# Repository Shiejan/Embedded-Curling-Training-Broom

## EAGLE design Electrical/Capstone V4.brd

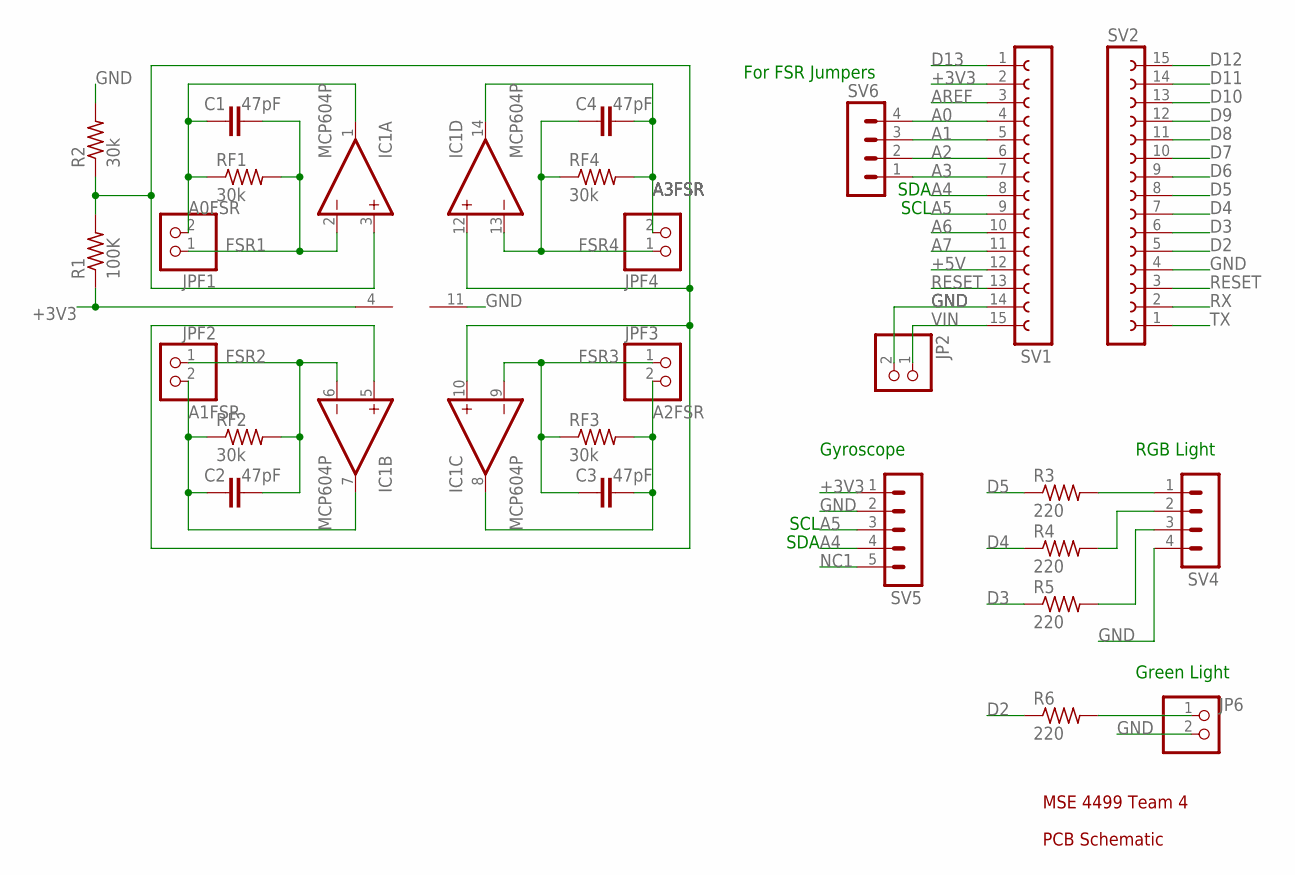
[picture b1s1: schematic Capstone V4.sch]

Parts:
C1, C2, C3, C4: 47pF; C2.5-3
IC1: MCP604P; DIL14
JP2, JP6: PINHD-1X2; 1X02
JPF1, JPF2, JPF3, JPF4: PINHD-1X2; 1X02
R1: 100K; 0204/7
R2: 30k; 0204/7
R3, R4, R5, R6: 220; 0204/7
RF1, RF2, RF3, RF4: 30k; 0204/7
SV1, SV2: FE15-1; FE15
SV4, SV6: MA04-1
SV5: MA05-1

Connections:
+3V3: IC1.4 (V+), R1.1, SV1.2, SV5.1
+5V: SV1.12
A0: SV1.4, SV6.4
A0FSR: C1.1, IC1.1 (OUT), JPF1.2, RF1.1
A1: SV1.5, SV6.3
A1FSR: C2.1, IC1.7 (OUT), JPF2.2, RF2.1
A2: SV1.6, SV6.2
A2FSR: C3.2, IC1.8 (OUT), JPF3.2, RF3.2
A3: SV1.7, SV6.1
A3FSR: C4.2, IC1.14 (OUT), JPF4.2, RF4.2
A4: SV1.8, SV5.4
A5: SV1.9, SV5.3
A6: SV1.10
A7: SV1.11
AREF: SV1.3
D2: R6.1, SV2.5
D3: R5.1, SV2.6
D4: R4.1, SV2.7
D5: R3.1, SV2.8
D6: SV2.9
D7: SV2.10
D8: SV2.11
D9: SV2.12
D10: SV2.13
D11: SV2.14
D12: SV2.15
D13: SV1.1
FSR1: C1.2, IC1.2 (-IN), JPF1.1, RF1.2
FSR2: C2.2, IC1.6 (-IN), JPF2.1, RF2.2
FSR3: C3.1, IC1.9 (-IN), JPF3.1, RF3.1
FSR4: C4.1, IC1.13 (-IN), JPF4.1, RF4.1
GND: IC1.11 (V-), JP2.2, JP6.2, R2.2, SV1.14, SV2.4, SV4.4, SV5.2
unnamed: R3.2, SV4.1
unnamed: R4.2, SV4.2
unnamed: R5.2, SV4.3
unnamed: JP6.1, R6.2
unnamed: IC1.3 (+IN), IC1.5 (+IN), IC1.10 (+IN), IC1.12 (+IN), R1.2, R2.1
NC1: SV5.5
RESET: SV1.13, SV2.3
RX: SV2.2
TX: SV2.1
VIN: JP2.1, SV1.15

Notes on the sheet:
RGB Light
Green Light
Gyroscope
SDA
SCL
For FSR Jumpers
PCB Schematic
MSE 4499 Team 4

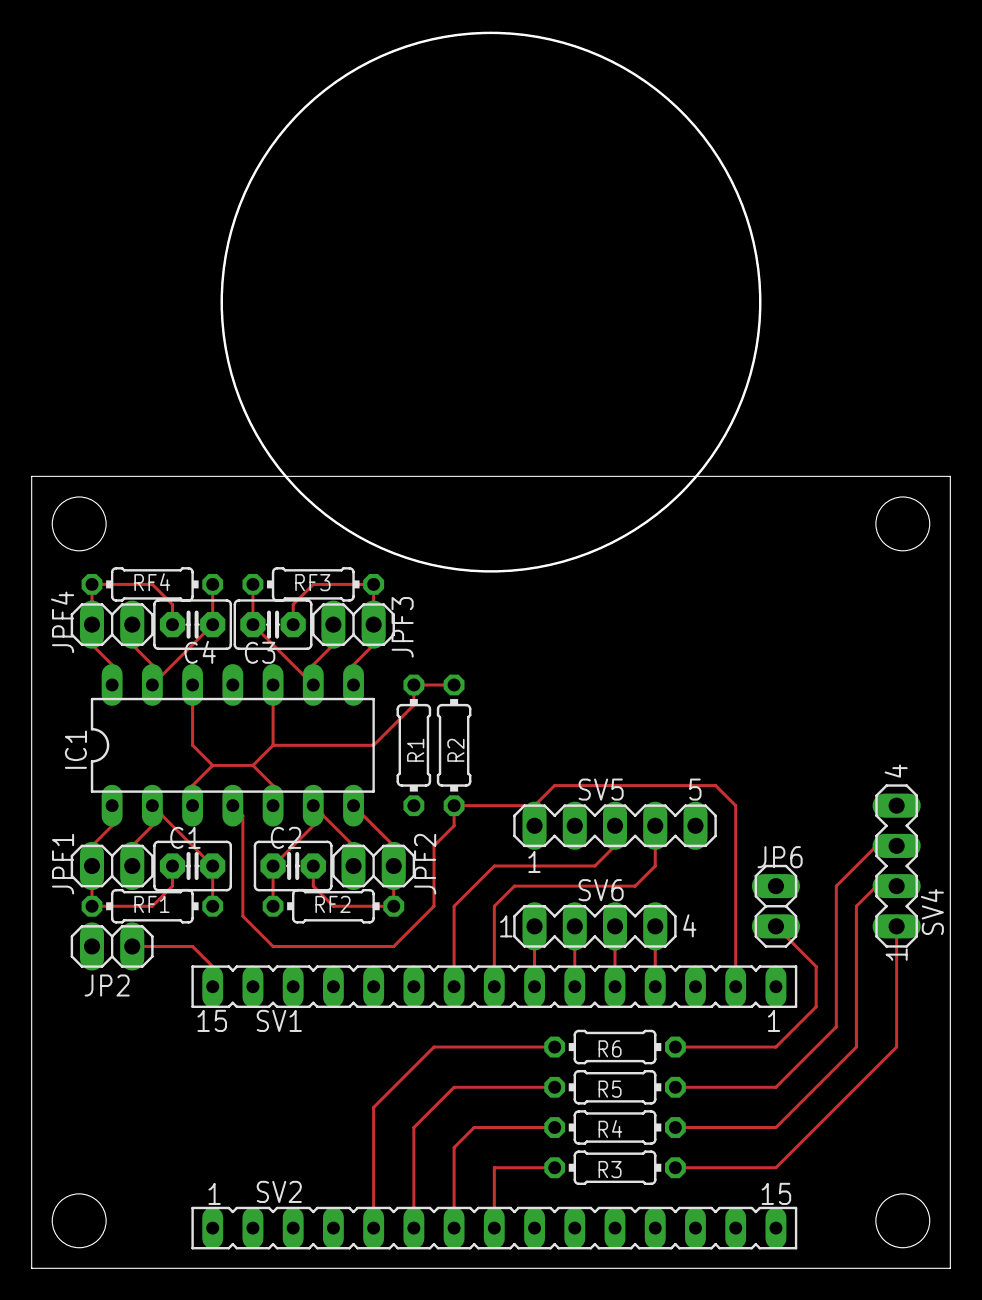
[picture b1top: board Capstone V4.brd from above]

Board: 2 copper layers, 57.8 x 77.9 mm, 26 parts (0 on the bottom side), 27 nets.

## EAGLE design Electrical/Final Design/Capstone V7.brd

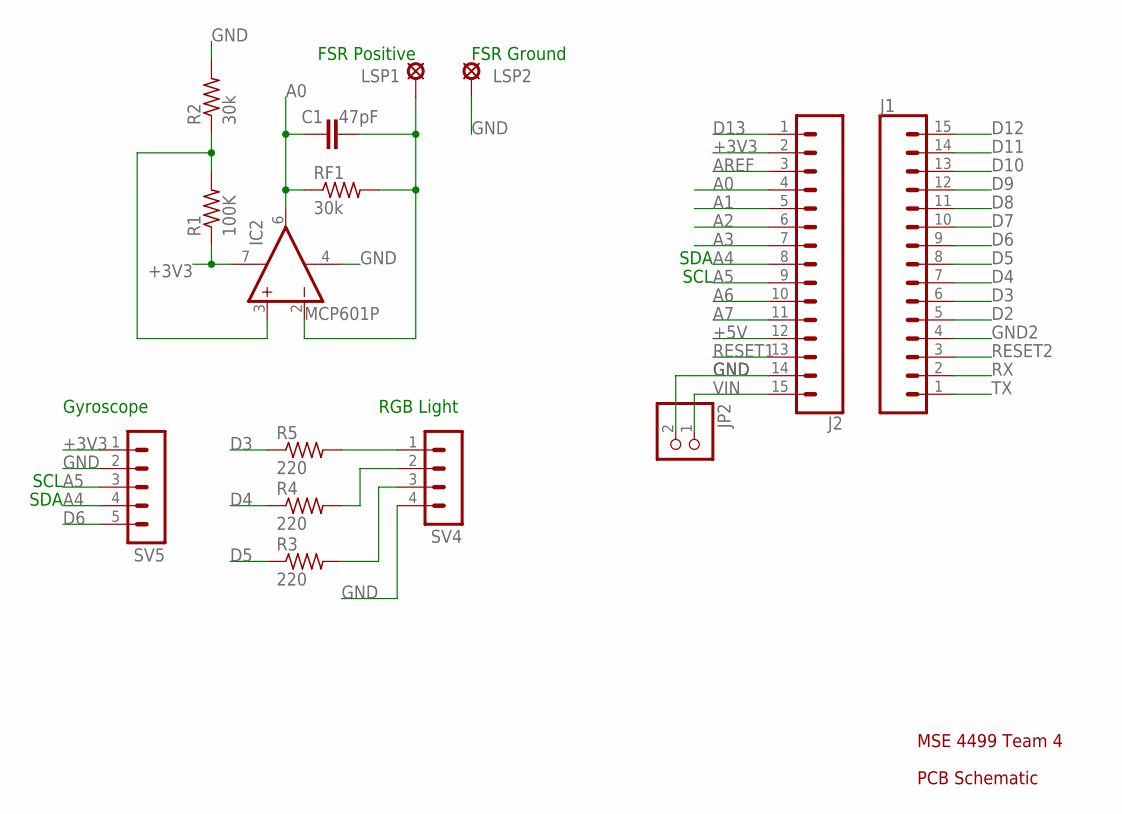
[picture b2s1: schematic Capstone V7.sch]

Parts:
C1: 47pF; C2.5-3
IC2: MCP601P; DIL08
J1, J2: CONN_15; 1X15
JP2: PINHD-1X2; 1X02
LSP1, LSP2: LSP10
R1: 100K; 0204/7
R2: 30k; 0204/7
R3, R4, R5: 220; 0204/7
RF1: 30k; 0204/7
SV4: MA04-1
SV5: MA05-1

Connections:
+3V3: IC2.7 (V+), J2.2, R1.1, SV5.1
+5V: J2.12
A0: C1.1, IC2.6 (OUT), J2.4, RF1.1
A1: J2.5
A2: J2.6
A3: J2.7
A4: J2.8, SV5.4
A5: J2.9, SV5.3
A6: J2.10
A7: J2.11
AREF: J2.3
D2: J1.5
D3: J1.6, R5.1
D4: J1.7, R4.1
D5: J1.8, R3.1
D6: J1.9, SV5.5
D7: J1.10
D8: J1.11
D9: J1.12
D10: J1.13
D11: J1.14
D12: J1.15
D13: J2.1
GND: IC2.4 (V-), J2.14, JP2.2, LSP2.MP, R2.2, SV4.4, SV5.2
GND2: J1.4
unnamed: R5.2, SV4.1
unnamed: IC2.3 (+IN), R1.2, R2.1
unnamed: R4.2, SV4.2
unnamed: R3.2, SV4.3
unnamed: C1.2, IC2.2 (-IN), LSP1.MP, RF1.2
RESET1: J2.13
RESET2: J1.3
RX: J1.2
TX: J1.1
VIN: J2.15, JP2.1

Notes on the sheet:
RGB Light
Gyroscope
SDA
SCL
PCB Schematic
MSE 4499 Team 4
FSR Ground
FSR Positive

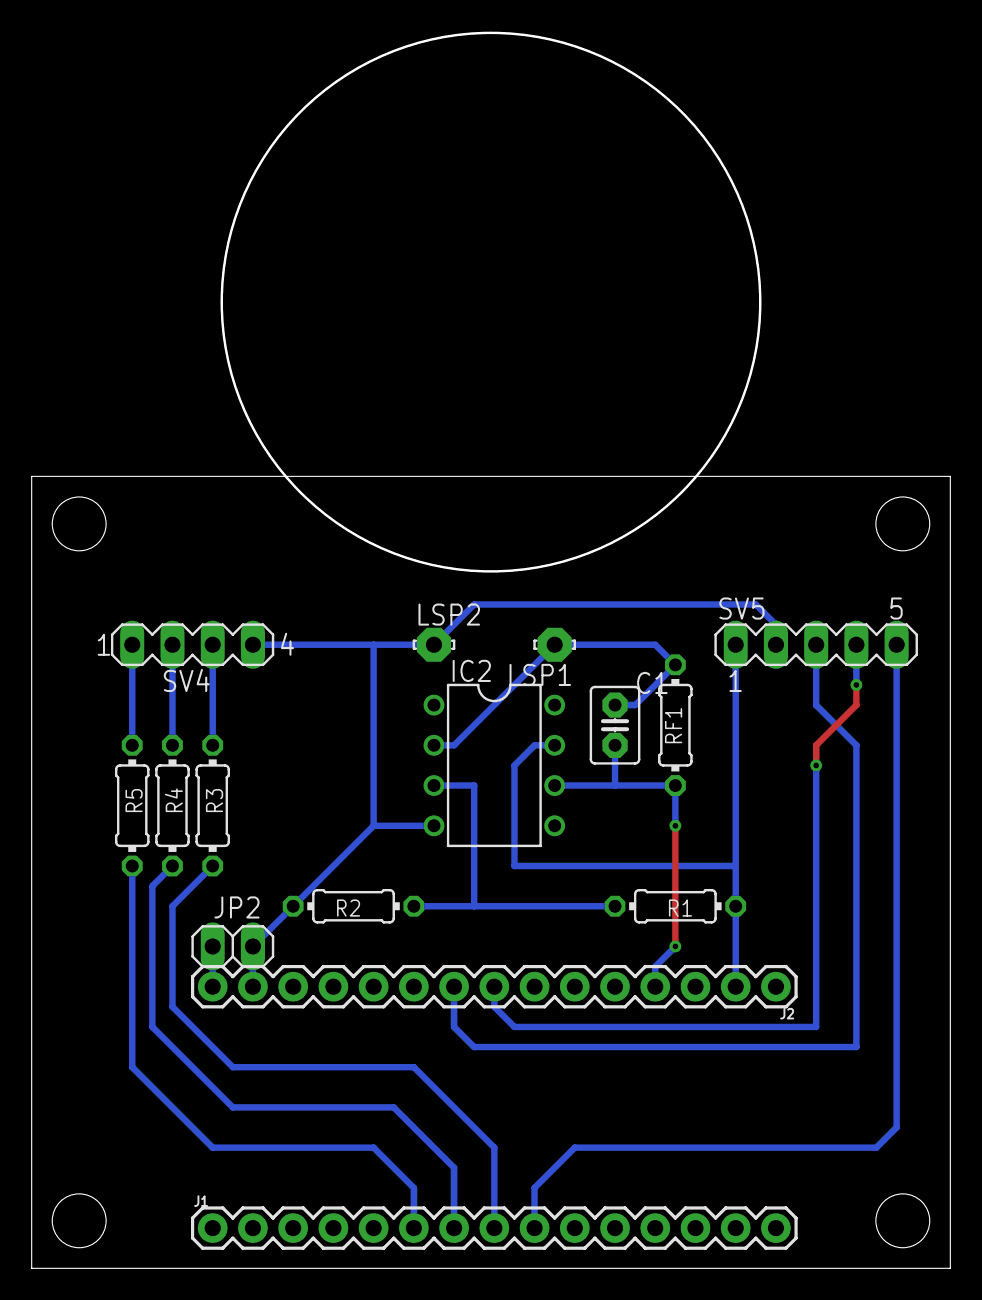
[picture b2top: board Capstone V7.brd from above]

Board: 2 copper layers, 57.8 x 77.9 mm, 15 parts (0 on the bottom side), 15 nets.

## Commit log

2023-01-04 Create Mechanical

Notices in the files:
parts and their libraries:
SparkFun-Connectors: Licensing: Creative Commons ShareAlike 4.0 International - https://creativecommons.org/licenses/by-sa/4.0
